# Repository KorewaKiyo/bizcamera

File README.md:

# BizCamera 
## A credit/business card sized camera

### Why?
I thought it was a cool and silly enough idea to be unique, and I couldn't find anyone else doing it. So I took it on myself to make it happen.

### How?
Initially I wanted to go with something STM32, as the camera module wants 1.8V, and there were some good STM32 MCUs with 1.8v, but it seemed like none of them were fast enough or had enough RAM to grab frames from the sensor. 
So I'm using the RP2350 which with PIO should have enough IO speed to just steal a frame off the data bus.

The chip itself doesn't have enough ram to store an image above 320x240 so I've added some RAM, a flash chip for code, and an SD card slot for storing images.

### What's the output like?
Yet to be seen :>

### What does the board look like?

rendered with [kicad-render](https://github.com/linalinn/kicad-render)

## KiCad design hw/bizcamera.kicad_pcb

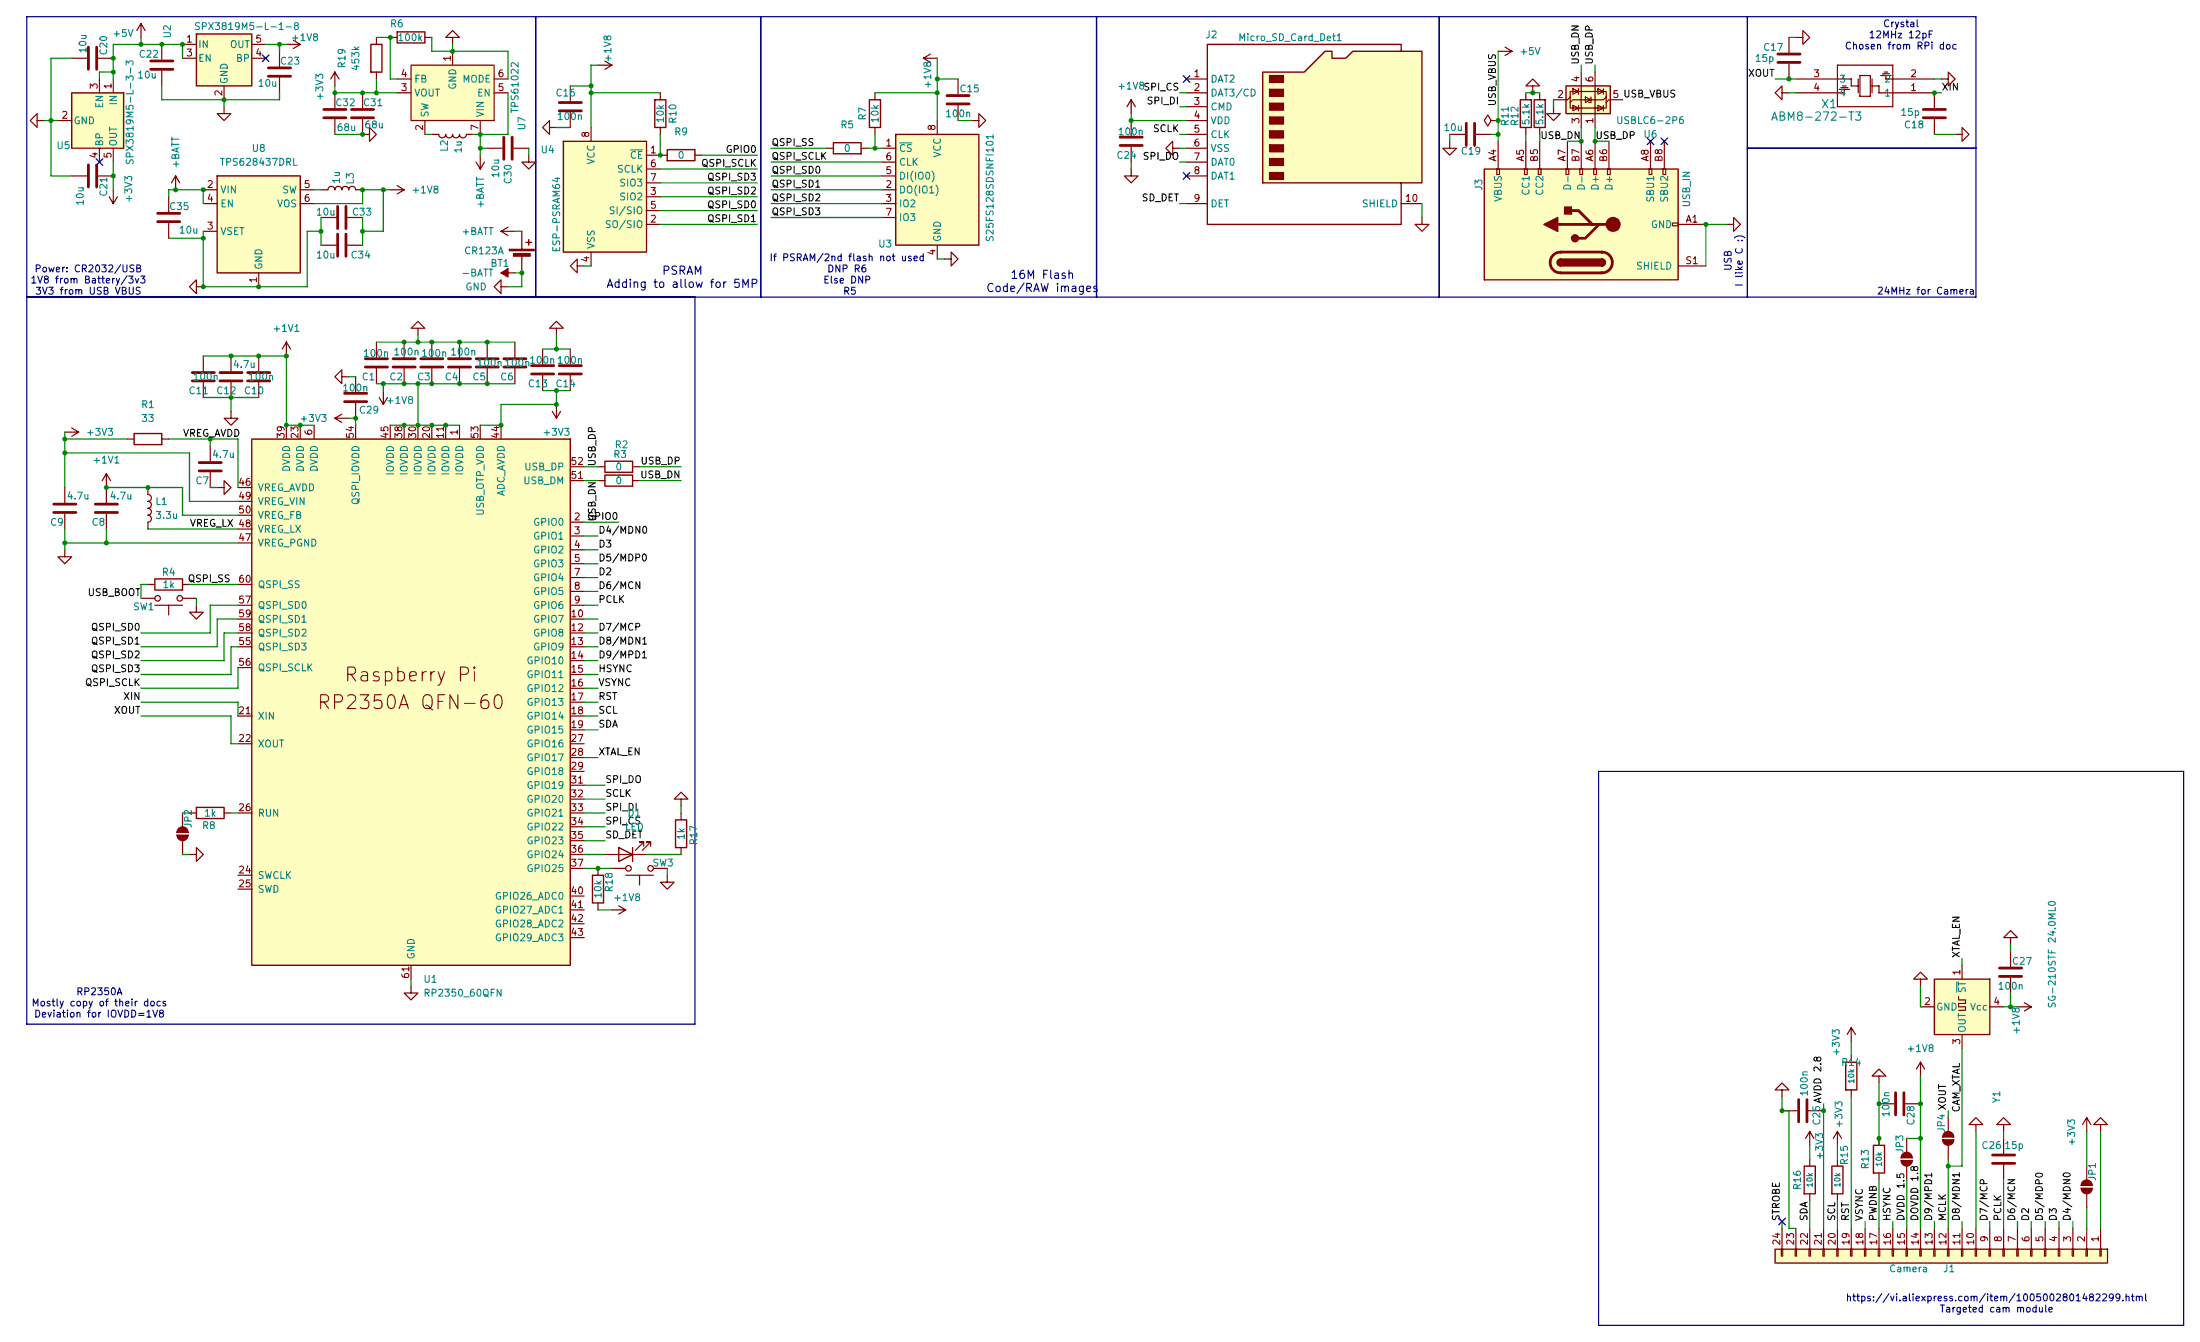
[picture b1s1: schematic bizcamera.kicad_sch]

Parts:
BT1: CR123A; BatteryHolder_Bulgin_BX0123_1xCR123
C1, C2, C3, C4, C5, C6, C10, C11, C13, C14, C15, C16, C24, C25, C27, C28, C29: 100n; C_0402_1005Metric; LCSC C1525
C7, C8, C9, C12: 4.7u; C_0402_1005Metric; LCSC C76995
C17, C18, C26: 15p; C_0402_1005Metric; LCSC C1548
C19, C20, C21, C22, C23, C30, C33, C34, C35: 10u; C_0603_1608Metric; LCSC C1691
C31, C32: 68u; C_0603_1608Metric; LCSC C7220
D1: LED; LED_1206_3216Metric_ReverseMount_Hole1.8x2.4mm; LCSC C329183
J1: Camera; Hirose_FH12-24S-0.5SH_1x24-1MP_P0.50mm_Horizontal; LCSC C202112
J2: Micro_SD_Card_Det1; microSD_HC_Hirose_DM3D-SF; LCSC C719027
J3: USB_IN; USB_C_Receptacle_HCTL_HC-TYPE-C-16P-01A; LCSC C2894897
JP1: CAM_AF; SolderJumper-2_P1.3mm_Open_RoundedPad1.0x1.5mm
JP2: USB_BOOT; SolderJumper-2_P1.3mm_Open_RoundedPad1.0x1.5mm
JP3: DVDD_1V8; SolderJumper-2_P1.3mm_Open_RoundedPad1.0x1.5mm
JP4: XTAL_JMP; SolderJumper-2_P1.3mm_Open_RoundedPad1.0x1.5mm
L1: 3.3u; L_pol_2016
L2, L3: 1u; TFM201610ALMA; LCSC C404808
R1: 33; R_0402_1005Metric; LCSC C25105
R2, R3, R5, R9: 0; R_0402_1005Metric; LCSC C17168
R4, R8, R17: 1k; R_0402_1005Metric; LCSC C11702
R6: 100k; R_0402_1005Metric_Pad0.72x0.64mm_HandSolder; LCSC C25741
R7, R10, R13, R14, R15, R16, R18: 10k; R_0603_1608Metric; LCSC C15401
R11, R12: 5.1k; R_0603_1608Metric; LCSC C23186
R19: 453k; R_0402_1005Metric_Pad0.72x0.64mm_HandSolder; LCSC C103049
SW1: USB_BOOT; SW_Push_1P1T_NO_CK_KMR2; LCSC C72443
SW3: Shutter; SW_Push_1P1T_NO_6x6mm_H9.5mm; LCSC C22397173
U1: RP2350_60QFN; RP2350-QFN-60-1EP_7x7_P0.4mm_EP3.4x3.4mm_ThermalVias; LCSC C42411118
U2: SPX3819M5-L-1-8; SOT-23-5; LCSC C18212663
U3: S25FS128SDSNFI101; WSON-8-1EP_6x5mm_P1.27mm_EP3.4x4.3mm; LCSC C2954241
U4: ESP-PSRAM64; SOIC-8_3.9x4.9mm_P1.27mm
U5: SPX3819M5-L-3-3; SOT-23-5; LCSC C5370980
U6: USBLC6-2P6; SOT-666; LCSC C2682291
U7: TPS61022; Texas_RWU0007A_VQFN-7_2x2mm_P0.5mm; LCSC C915088
U8: TPS628437DRL; SOT-563; LCSC C25838674
X1: ABM8-272-T3; ABM8-272-T3_ABR; LCSC C20625731
Y1: SG-210STF 24.0ML0; Oscillator_SMD_SeikoEpson_SG210-4Pin_2.5x2.0mm

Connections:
+1V1: C8.1, C10.1, C11.1, C12.1, L1.1, U1.6 (DVDD), U1.23 (DVDD), U1.39 (DVDD), U1.50 (VREG_FB)
+1V8: C1.2, C2.2, C3.2, C4.2, C5.2, C6.2, C15.2, C16.2, C23.1, C24.1, C27.1, C28.2, C33.1, C34.1, J1.14, J2.4 (VDD), JP3.1 (A), L3.2, R7.2, R10.2, R18.1, U1.1 (IOVDD), U1.11 (IOVDD), U1.20 (IOVDD), U1.30 (IOVDD), U1.38 (IOVDD), U1.45 (IOVDD), U2.5 (OUT), U3.8 (VCC), U4.8 (VCC), U8.6 (VOS), Y1.4 (Vcc)
+3V3: C9.1, C13.2, C14.2, C21.1, C29.2, C31.1, C32.1, JP1.1 (A), R1.1, R14.1, R15.1, R16.1, R19.2, U1.44 (ADC_AVDD), U1.49 (VREG_VIN), U1.53 (USB_OTP_VDD), U1.54 (QSPI_IOVDD), U5.5 (OUT), U7.3 (VOUT)
+5V: C19.2, C20.1, C22.1, J3.A4 (VBUS), J3.A9 (VBUS), J3.B4 (VBUS), J3.B9 (VBUS), U2.1 (IN), U2.3 (EN), U5.1 (IN), U5.3 (EN), U6.5 (VBUS)
+BATT: BT1.1 (+), C30.2, C35.1, L2.1, U7.5 (EN), U7.7 (VIN), U8.2 (VIN), U8.4 (EN)
-BATT: BT1.2 (-), C1.1, C2.1, C3.1, C4.1, C5.1, C6.1, C7.2, C8.2, C9.2, C10.2, C11.2, C12.2, C13.1, C14.1, C15.1, C16.1, C17.2, C18.2, C19.1, C20.2, C21.2, C22.2, C23.2, C24.2, C25.1, C26.1, C27.2, C28.1, C29.1, C30.1, C31.2, C32.2, C33.2, C34.2, C35.2, J1.1, J1.10, J1.23, J2.6 (VSS), J2.10 (SHIELD), J3.A1 (GND), J3.A12 (GND), J3.B1 (GND), J3.B12 (GND), J3.S1 (SHIELD), JP2.2 (B), R6.1, R11.2, R12.2, R13.1, R17.1, SW1.1, SW3.1, U1.47 (VREG_PGND), U1.61 (GND), U2.2 (GND), U3.4 (GND), U4.4 (VSS), U5.2 (GND), U6.2 (GND), U7.1 (GND), U7.6 (MODE), U8.1 (GND), U8.3 (VSET), X1.2, X1.4, Y1.2 (GND)
/AVDD 2.8: C25.2, J1.21
/CAM_XTAL: J1.12, JP4.2 (B), Y1.3 (OUT)
/D2: J1.6, U1.7 (GPIO4)
/D3: J1.4, U1.4 (GPIO2)
/D4/MDN0: J1.3, U1.3 (GPIO1)
/D5/MDP0: J1.5, U1.5 (GPIO3)
/D6/MCN: J1.7, U1.8 (GPIO5)
/D7/MCP: J1.9, U1.12 (GPIO8)
/D8/MDN1: J1.11, U1.13 (GPIO9)
/D9/MPD1: J1.13, U1.14 (GPIO10)
/DVDD 1.5: J1.15, JP3.2 (B)
/GPIO0: R9.1, U1.2 (GPIO0)
/HSYNC: J1.16, U1.15 (GPIO11)
/PCLK: C26.2, J1.8, U1.9 (GPIO6)
/PWDNB: J1.17, R13.2
/QSPI_SCLK: U1.56 (QSPI_SCLK), U3.6 (CLK), U4.6 (SCLK)
/QSPI_SD0: U1.57 (QSPI_SD0), U3.5 (DI(IO0)), U4.5 (SI/SIO)
/QSPI_SD1: U1.59 (QSPI_SD1), U3.2 (DO(IO1)), U4.2 (SO/SIO)
/QSPI_SD2: U1.58 (QSPI_SD2), U3.3 (IO2), U4.3 (SIO2)
/QSPI_SD3: U1.55 (QSPI_SD3), U3.7 (IO3), U4.7 (SIO3)
/QSPI_SS: R4.2, R5.1, U1.60 (QSPI_SS)
/RST: J1.19, R14.2, U1.17 (GPIO13)
/SCL: J1.20, R15.2, U1.18 (GPIO14)
/SCLK: J2.5 (CLK), U1.32 (GPIO20)
/SDA: J1.22, R16.2, U1.19 (GPIO15)
/SD_DET: J2.9 (DET), U1.35 (GPIO23)
/SPI_CS: J2.2 (DAT3/CD), U1.34 (GPIO22)
/SPI_DI: J2.3 (CMD), U1.33 (GPIO21)
/SPI_DO: J2.7 (DAT0), U1.31 (GPIO19)
/STROBE: J1.24
/USB_BOOT: R4.1, SW1.2
/USB_DN: J3.A7 (D-), J3.B7 (D-), R3.1, R3.2, U1.51 (USB_DM), U6.3 (I/O2), U6.4 (I/O2)
/USB_DP: J3.A6 (D+), J3.B6 (D+), R2.1, R2.2, U1.52 (USB_DP), U6.1 (I/O1), U6.6 (I/O1)
/VREG_AVDD: C7.1, R1.2, U1.46 (VREG_AVDD)
/VREG_LX: L1.2, U1.48 (VREG_LX)
/VSYNC: J1.18, U1.16 (GPIO12)
/XIN: C18.1, U1.21 (XIN), X1.1
/XOUT: C17.1, JP4.1 (A), U1.22 (XOUT), X1.3
/XTAL_EN: U1.28 (GPIO17), Y1.1 (~ST)
unnamed: D1.2 (A), U1.36 (GPIO24)
unnamed: D1.1 (K), R17.2
unnamed: J1.2, JP1.2 (B)
unnamed: J3.A5 (CC1), R11.1
unnamed: J3.B5 (CC2), R12.1
unnamed: JP2.1 (A), R8.2
unnamed: R18.2, SW3.2, U1.37 (GPIO25)
unnamed: R8.1, U1.26 (RUN)
unnamed: R5.2, R7.1, U3.1 (~CS)
unnamed: R9.2, R10.1, U4.1 (~CE)
unnamed: R6.2, R19.1, U7.4 (FB)
unnamed: L2.2, U7.2 (SW)
unnamed: L3.1, U8.5 (SW)

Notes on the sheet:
16M Flash Code/RAW images
USB I like C :)
Crystal 12MHz 12pF Chosen from RPi doc
If PSRAM/2nd flash not used DNP R6 Else DNP R5
Power: CR2032/USB 1V8 from Battery/3v3 3V3 from USB VBUS
24MHz for Camera
PSRAM Adding to allow for 5MP
RP2350A Mostly copy of their docs Deviation for IOVDD=1V8
https://vi.aliexpress.com/item/1005002801482299.html Targeted cam module

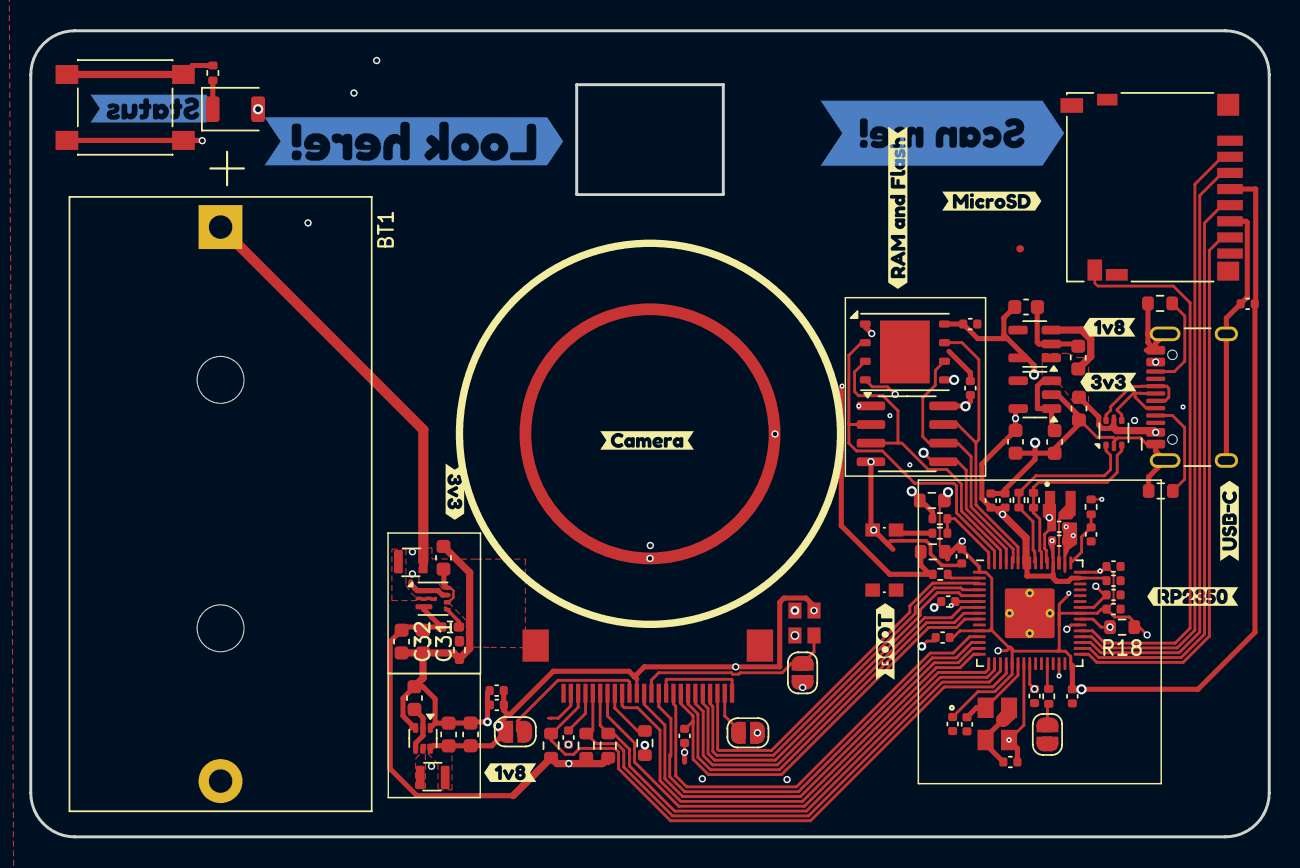
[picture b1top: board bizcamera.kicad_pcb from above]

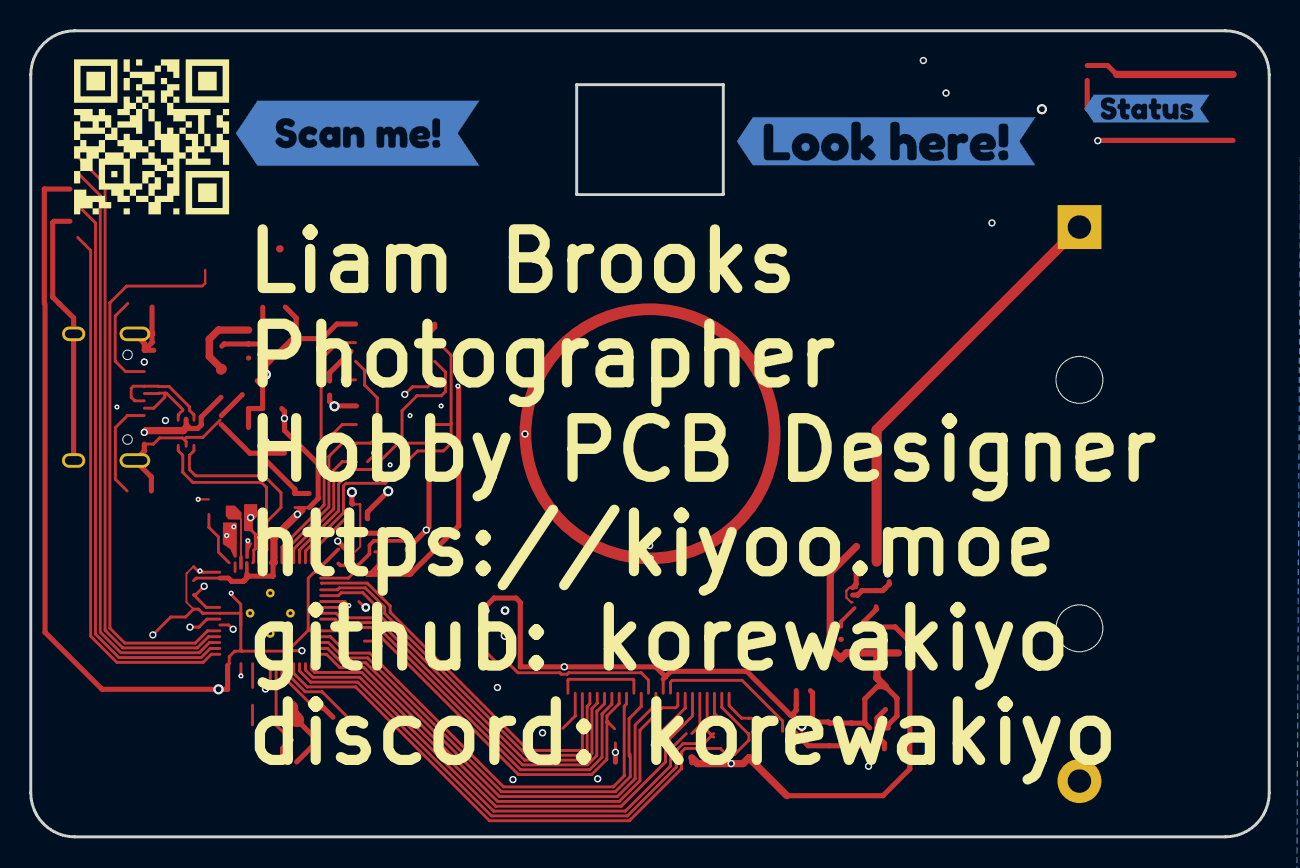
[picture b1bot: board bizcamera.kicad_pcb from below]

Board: 4 copper layers, 84.5 x 55.0 mm, 92 parts (3 on the bottom side), 57 nets.

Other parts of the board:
kibuzzard-6825B58C: G***; kibuzzard-6825B58C
kibuzzard-68265B48: G***; kibuzzard-68265B48
kibuzzard-68265CCE: G***; kibuzzard-68265CCE
kibuzzard-68265CF0: G***; kibuzzard-68265CF0
kibuzzard-68265EBA: G***; kibuzzard-68265EBA
kibuzzard-68265EEF: G***; kibuzzard-68265EEF
kibuzzard-68265F1C: G***; kibuzzard-68265F1C
kibuzzard-68265F3A: G***; kibuzzard-68265F3A
kibuzzard-68265F49: G***; kibuzzard-68265F49
kibuzzard-68265FBA: G***; kibuzzard-68265FBA
kibuzzard-68265FD3: G***; kibuzzard-68265FD3
kibuzzard-68265FDC: G***; kibuzzard-68265FDC
kibuzzard-682743A4: G***; kibuzzard-682743A4
kibuzzard-68266036: G***; kibuzzard-68266036

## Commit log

2025-04-29 Define project
    Define pcb edge cuts
2025-05-01 Schematic rev1
    Rev1 of the schematic, not finished, but close.
    Switched to rp2350 because PIO is powerful enough to grab frames without DCMI iface
2025-05-02 Finish schematic
2025-05-15 Near final design
    Near final design for prototype model, for both schematic and PCB
    Layout was an absolute nightmare. But I think this is the best I can do with the constraints, and it should look pretty nice too.
2025-05-15 Tidy up
2025-05-15 Styling
    Styling to make it more of a business card :D
2025-05-16 BOM and minor rework
    I realised 68u 0603's were impossible lol
2025-12-16 Directory update
